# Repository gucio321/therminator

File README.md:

# Intro

This is a repository containing resources for my enviroumental physics project.

# Goals

The main goal of this project is to compare various types of thermal sensors in terms of their accuracy.

The expected result of the experiment is a decent set of data obtained automatically with a microcontroller setup.

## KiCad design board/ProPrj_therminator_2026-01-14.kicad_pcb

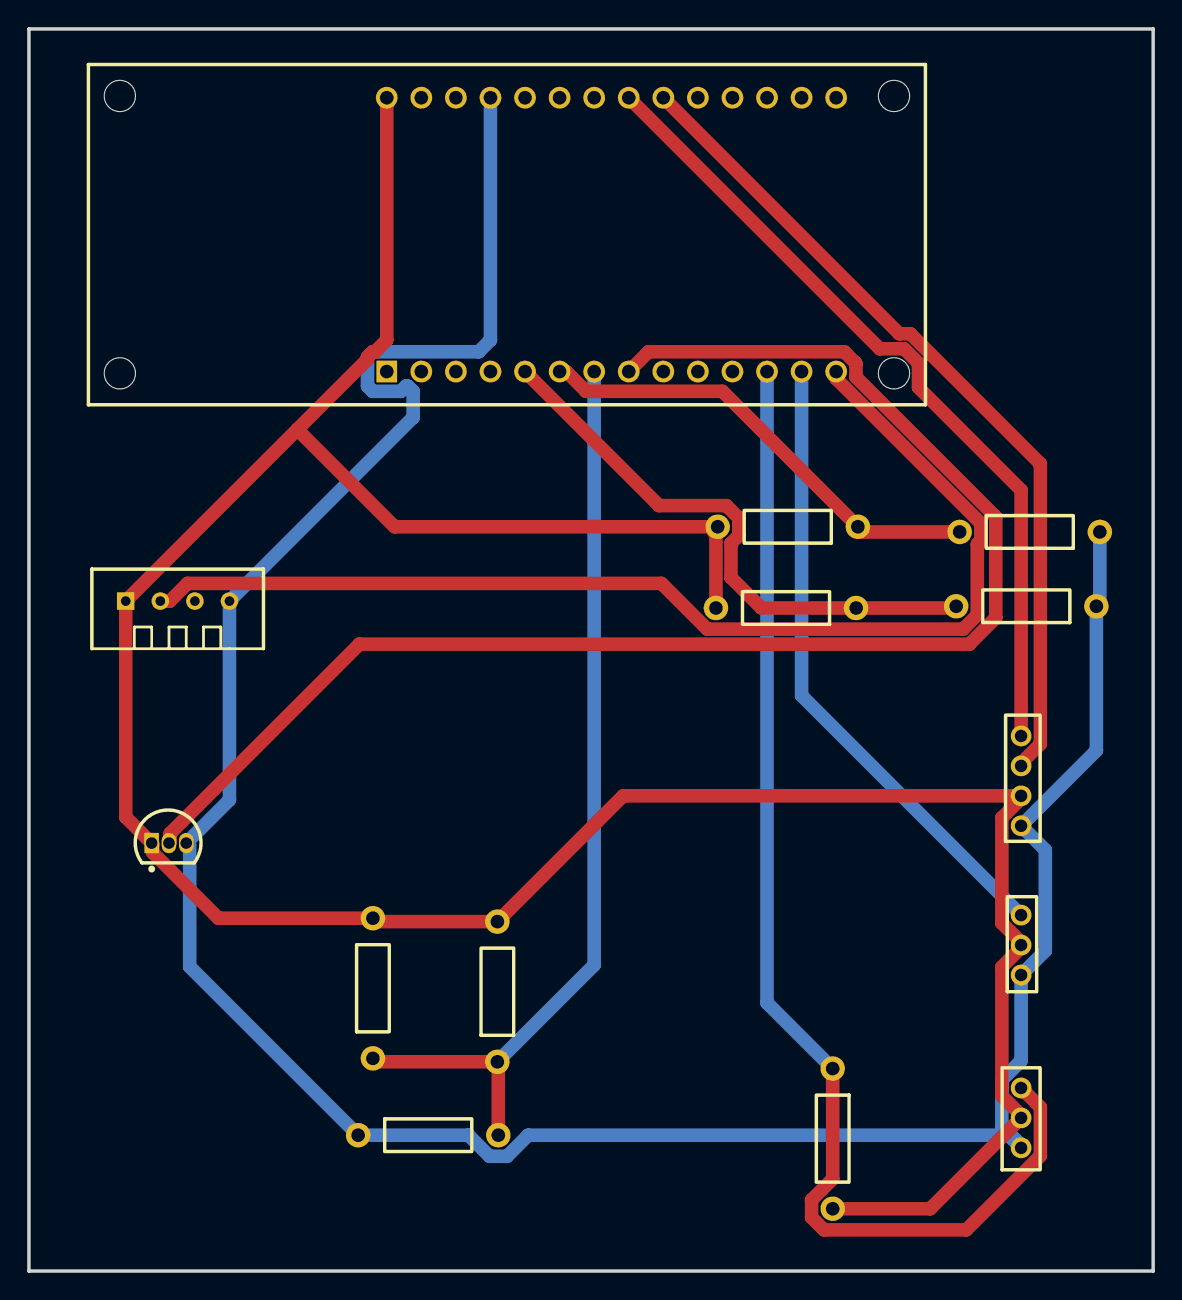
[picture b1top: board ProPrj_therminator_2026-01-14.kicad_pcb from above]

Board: 2 copper layers, 82.6 x 91.3 mm, 14 parts (0 on the bottom side), 11 nets.

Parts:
DHT11: SENSOR-TH_DHT11-1
DHT22: DHT22-cable
DS18B20-1: DS18B20-cable
LCD-1: LCD-cable
LM35: TO-92-3_L4.8-W3.7-P1.27-L
NTC: RES-TH_BD2.3-L6.3-P10.30-D0.6
PT100-1, PT100-2: RES-TH_BD2.3-L6.3-P10.30-D0.6
R4: RES-TH_BD2.3-L6.3-P10.30-D0.6
RPom1, RPom2, RPom3, RPom4: RES-TH_BD2.3-L6.3-P10.30-D0.6
U1: COMM-TH_28P-L61.5-W25.0-P2.54

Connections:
$1N461: DHT11.1, DHT22.2, DS18B20-1.2, LCD-1.2, LM35.1, R4.2, RPom1.2, RPom2.2, RPom3.2, RPom4.2, U1.28
$1N571: DHT11.2, U1.14
$1N609: LM35.2, U1.8
$1N615: DHT11.4, DHT22.1, DS18B20-1.1, LCD-1.1, LM35.3, NTC.1, PT100-1.1, PT100-2.1, U1.25
$1N842: NTC.2, RPom1.1, RPom2.1, U1.7
$1N1258: DHT22.3, U1.13
$1N1408: DS18B20-1.3, R4.1, U1.12
$1N1586: PT100-1.2, RPom3.1, U1.6
$1N1590: PT100-2.2, RPom4.1, U1.5
$1N1838: LCD-1.3, U1.20
$1N1847: LCD-1.4, U1.21

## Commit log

2025-12-19 therminator: add dht11 support
2025-12-19 therminator implement some sensors
2025-12-20 implement lcd
2025-12-20 add sd support
2025-12-21 add pt100 impl
2026-01-08 pt100: adjust values and cosider wires resistance
2026-01-11 improve data file and overall data exported
2026-01-17 add board info
